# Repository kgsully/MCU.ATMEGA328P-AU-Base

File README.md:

# ATMEGA328P-AU Base Design
 ATMEGA328P-AU Base Design

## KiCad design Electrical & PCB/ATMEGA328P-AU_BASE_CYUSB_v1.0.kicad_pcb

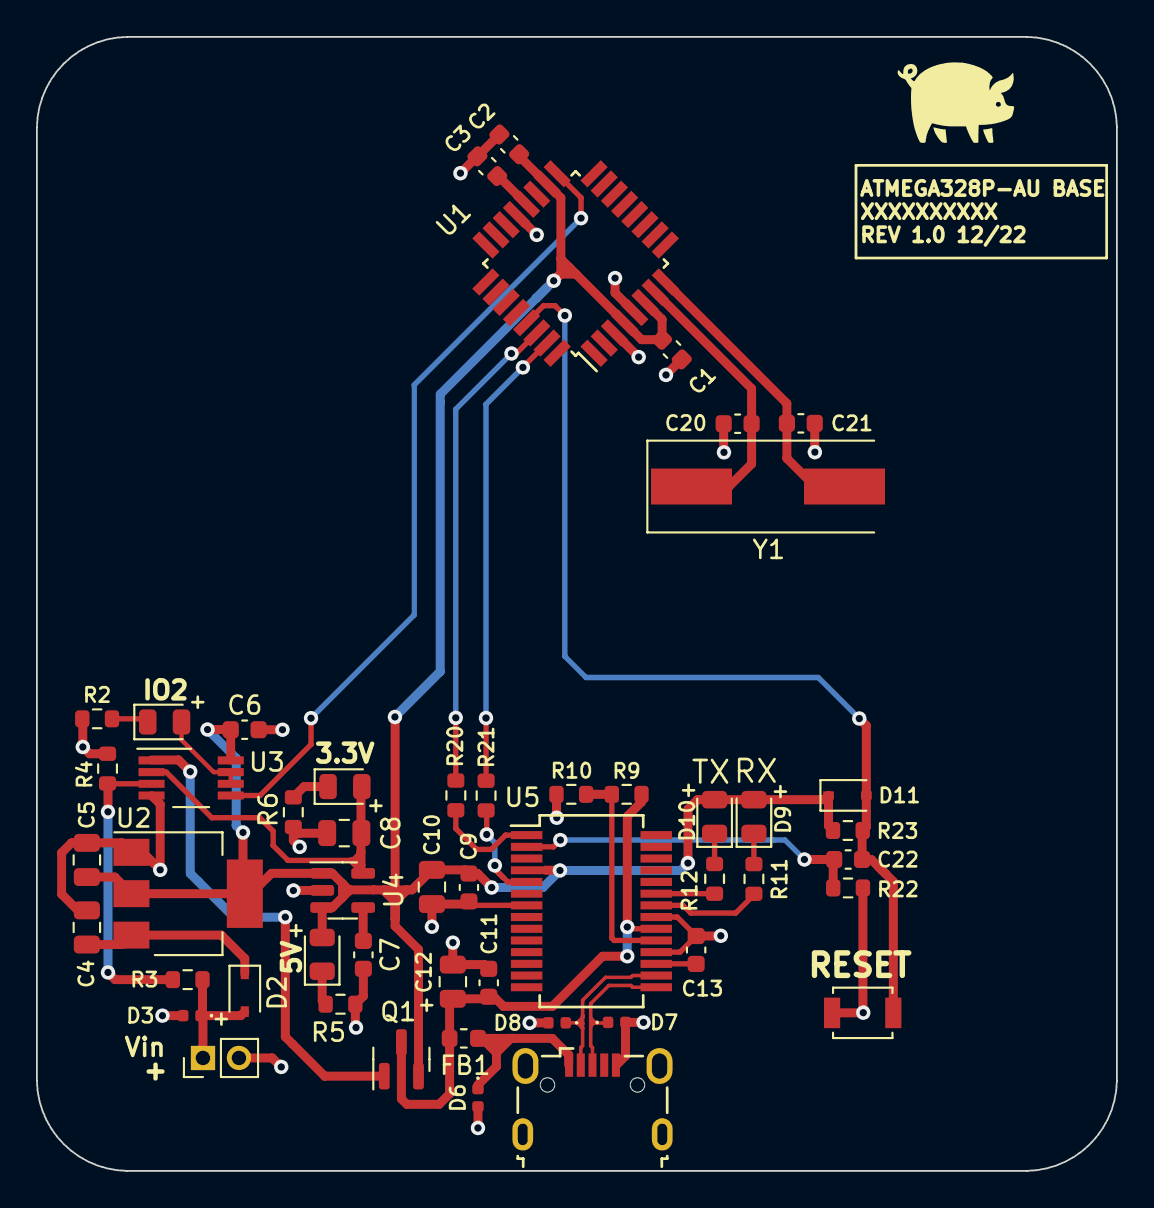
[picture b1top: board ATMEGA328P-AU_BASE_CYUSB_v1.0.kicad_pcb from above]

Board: 2 copper layers, 60.0 x 63.0 mm, 51 parts (0 on the bottom side), 32 nets.

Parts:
C1, C2, C3, C9, C11, C22: 0.1u; C_0603_1608Metric
C4: 1u; C_0805_2012Metric
C5: 4u7; C_0805_2012Metric
C6: 100n; C_0603_1608Metric
C7: 10n; C_0603_1608Metric
C8: 2.2u; C_0805_2012Metric
C10, C12: 4.7u; C_0805_2012Metric
C13: 1u; C_0603_1608Metric
C20, C21: 22p; C_0603_1608Metric
D1: BLU; LED_0805_2012Metric
D2: BAT760-7; D_SOD-323
D3, D6, D7, D8: 5VWM; D_0402_1005Metric
D4: RED; LED_0805_2012Metric
D5, D9, D10: GRN; LED_0805_2012Metric
D11: 1N4148WS; D_SOD-323
FB1: 40-100R; L_0603_1608Metric
J2: Conn_01x02_Male; PinHeader_1x02_P2.00mm_Vertical
J3: USB_B_Micro; USB_Micro-B_Wuerth_629105150521
Q1: DMP2110U-7; SOT-23
R2: 470R; R_0603_1608Metric
R3, R4, R10, R23: 10k; R_0603_1608Metric
R5, R6, R11, R12, R20, R21, R22: 1k; R_0603_1608Metric
R9: 4k7; R_0603_1608Metric
SW1: RESET; SW_SPST_B3U-1000P
U1: ATmega328P-AU; TQFP-32_7x7mm_P0.8mm
U2: LDL1117S50R; SOT-223-3_TabPin2
U3: LMV358IDGKR; VSSOP-8_3.0x3.0mm_P0.65mm
U4: SPX3819M5-L-3-3; SOT-23-5
U5: CY7C65213-28PVXI; SSOP-28_5.3x10.2mm_P0.65mm
Y1: 16MHZ; Crystal_SMD_HC49-SD

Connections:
+3.3V: C8.1, D5.2 (A), U3.2 (-), U4.5 (OUT)
+5V: C1.1, C2.1, C5.1, C6.1, C9.2, C10.1, D4.2 (A), D9.2 (A), D10.2 (A), D11.1 (K), Q1.2 (S), R23.1, U1.4 (VCC), U1.6 (VCC), U1.18 (AVCC), U2.2 (VO), U3.8 (V+), U4.1 (IN), U4.3 (EN), U5.4 (VCCIO)
/ATMega328P-AU MCU/AREF: C3.1, U1.20 (AREF)
/ATMega328P-AU MCU/DTR: C22.1, R22.1, U5.2 (DTR)
/ATMega328P-AU MCU/IO13/SCK: U1.17 (IO13/PB5), U3.5 (+)
/ATMega328P-AU MCU/RXD/IO0: R20.2, U5.1 (TXD)
/ATMega328P-AU MCU/TXD/IO1: R21.2, U5.5 (RXD)
/Power Supply/VBUS: C11.2, C12.1, FB1.2, Q1.3 (D), R9.2, U5.20 (VCC)
/Power Supply/VIN: D2.2 (A), D3.1 (A1), J2.1, R3.1
/USB-UART Interface/USB_D+: D7.1 (A1), J3.3 (D+), U5.15 (USBDP)
/USB-UART Interface/USB_D-: D8.1 (A1), J3.2 (D-), U5.16 (USBDM)
GND: C1.2, C2.2, C3.2, C4.2, C5.2, C6.2, C7.2, C8.2, C9.1, C10.2, C11.1, C12.2, C13.2, C20.1, C21.1, D3.2 (A2), D6.2 (A2), D7.2 (A2), D8.2 (A2), J2.2, J3.5 (GND), R2.2, R4.2, R5.2, R6.2, R10.1, R22.2, SW1.2, U1.3 (GND), U1.5 (GND), U1.21 (GND), U2.1 (GND), U3.4 (V-), U4.2 (GND), U5.7 (GND), U5.18 (GND), U5.21 (GND)
unnamed: C4.1, D2.1 (K), U2.3 (VI)
unnamed: C7.1, U4.4 (BP)
unnamed: C13.1, U5.17 (VCCD)
unnamed: C20.2, U1.7 (XTAL1/PB6), Y1.1
unnamed: C21.2, U1.8 (XTAL2/PB7), Y1.2
unnamed: C22.2, D11.2 (A), R23.2, SW1.1, U1.29 (~RESET/PC6)
unnamed: D1.1 (K), R2.1
unnamed: D1.2 (A), U3.6 (-), U3.7
unnamed: D4.1 (K), R5.1
unnamed: D5.1 (K), R6.1
unnamed: D6.1 (A1), FB1.1, J3.1 (VBUS)
unnamed: D9.1 (K), R11.2
unnamed: D10.1 (K), R12.2
unnamed: Q1.1 (G), U3.1
unnamed: R3.2, R4.1, U3.3 (+)
unnamed: R11.1, U5.22 (GPIO1)
unnamed: R12.1, U5.23 (GPIO0)
unnamed: R20.1, U1.30 (IO0/PD0)
unnamed: R21.1, U1.31 (IO1/PD1)
unnamed: R9.1, R10.2, U5.19 (~RESET)
